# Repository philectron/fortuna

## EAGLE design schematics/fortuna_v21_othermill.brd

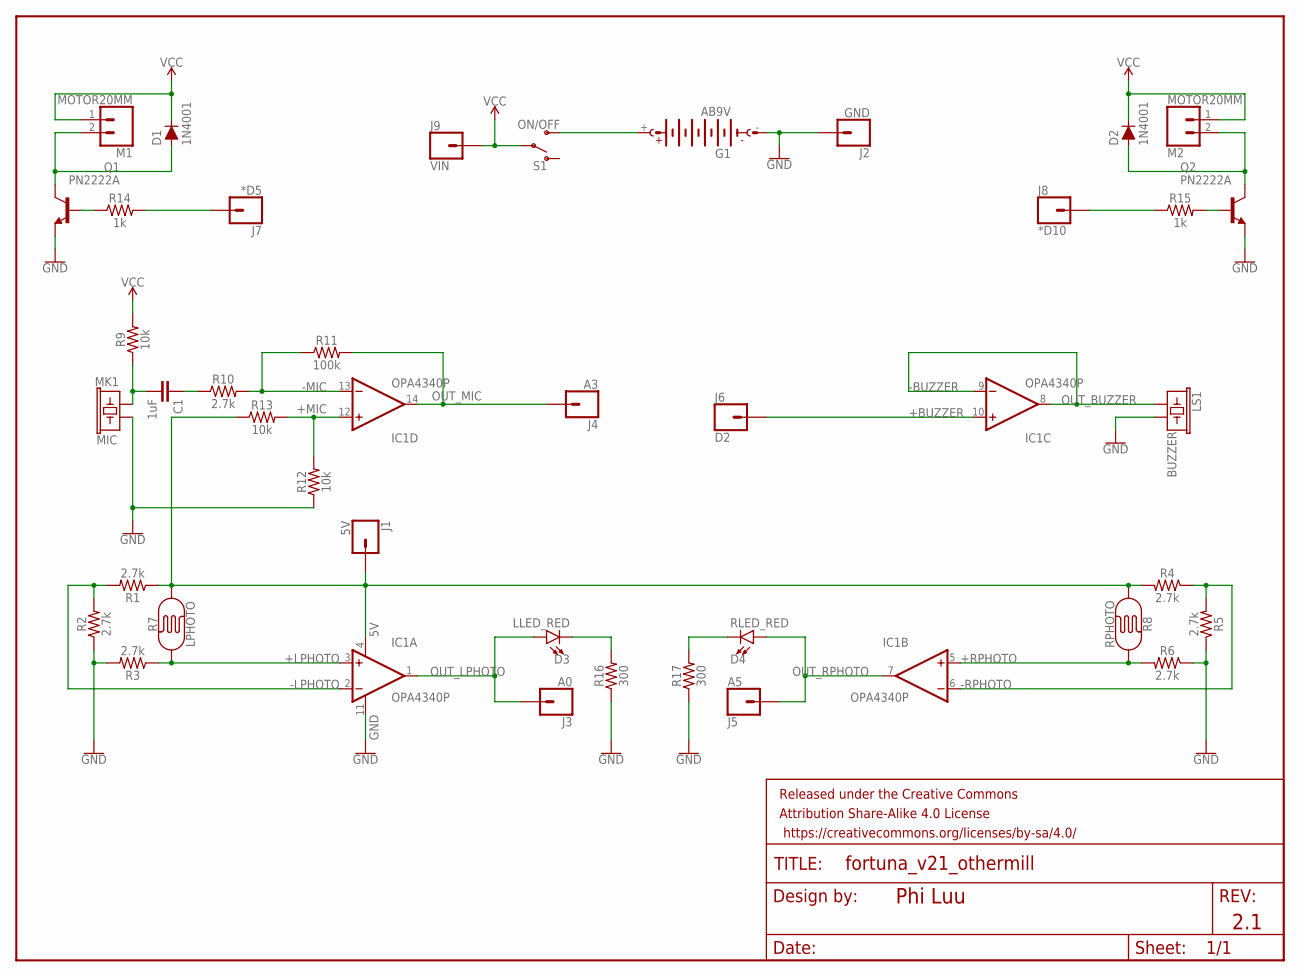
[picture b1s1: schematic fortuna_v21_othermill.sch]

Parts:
C1: 1uF; CAP-PTH-SMALL-KIT
D1, D2: 1N4001; DIODE-1N4001
D3: LLED_RED; LED_5MM
D4: RLED_RED; LED_5MM
FRAME1: FRAME-LETTER; CREATIVE_COMMONS
G1: AB9V
IC1: OPA4340P; DIL14
J1: 5V; 1X01
J2: GND; 1X01
J3: A0; 1X01
J4: A3; 1X01
J5: A5; 1X01
J6: D2; 1X01
J7: *D5; 1X01
J8: *D10; 1X01
J9: VIN; 1X01
LS1: BUZZER; BUZZER-12MM
M1, M2: MOTOR20MM; 1X02
MK1: MIC; MICROPHONE-PTH-9.7MM
Q1, Q2: PN2222A; TO92-EBC-OVAL
R1, R2, R3, R4, R5, R6, R10: 2.7k; AXIAL-0.3
R7: LPHOTO; PHOTOCELL
R8: RPHOTO; PHOTOCELL
R9, R12, R13: 10k; AXIAL-0.3
R11: 100k; AXIAL-0.3
R14, R15: 1k; AXIAL-0.3
R16, R17: 300; AXIAL-0.3
S1: ON/OFF; SWITCH_SPDT_PTH_11.6X4.0MM

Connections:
5V: IC1.4 (V+), J1.1, R1.P$1 (1), R4.P$2 (2), R7.2, R8.2, R13.P$1 (1)
9V: G1.+, S1.3 (S)
+BUZZER: IC1.10 (+IN), J6.1
+LPHOTO: IC1.3 (+IN), R3.P$1 (1), R7.1
+MIC: IC1.12 (+IN), R12.P$2 (2), R13.P$2 (2)
+RPHOTO: IC1.5 (+IN), R6.P$2 (2), R8.1
-LPHOTO: IC1.2 (-IN), R1.P$2 (2), R2.P$2 (2)
-MIC: IC1.13 (-IN), R10.P$2 (2), R11.P$1 (1)
-RPHOTO: IC1.6 (-IN), R4.P$1 (1), R5.P$2 (2)
GND: G1.-, IC1.11 (V-), J2.1, LS1.- (2), MK1.GND (2), Q1.E, Q2.E, R2.P$1 (1), R3.P$2 (2), R5.P$1 (1), R6.P$1 (1), R12.P$1 (1), R16.P$1 (1), R17.P$1 (1)
unnamed: C1.2, MK1.OUT (1), R9.P$1 (1)
unnamed: C1.1, R10.P$1 (1)
unnamed: D3.K (C), R16.P$2 (2)
unnamed: D4.K (C), R17.P$2 (2)
unnamed: Q1.B, R14.P$1 (1)
unnamed: D1.A, M1.2, Q1.C
unnamed: D2.A, M2.2, Q2.C
unnamed: Q2.B, R15.P$2 (2)
OUT_BUZZER: IC1.8 (OUT), IC1.9 (-IN), LS1.+ (1)
OUT_LMOTOR: J7.1, R14.P$2 (2)
OUT_LPHOTO: D3.A, IC1.1 (OUT), J3.1
OUT_MIC: IC1.14 (OUT), J4.1, R11.P$2 (2)
OUT_RMOTOR: J8.1, R15.P$1 (1)
OUT_RPHOTO: D4.A, IC1.7 (OUT), J5.1
VCC: D1.C, D2.C, J9.1, M1.1, M2.1, R9.P$2 (2), S1.2

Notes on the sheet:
Phi Luu
2.1
+BUZZER
-BUZZER

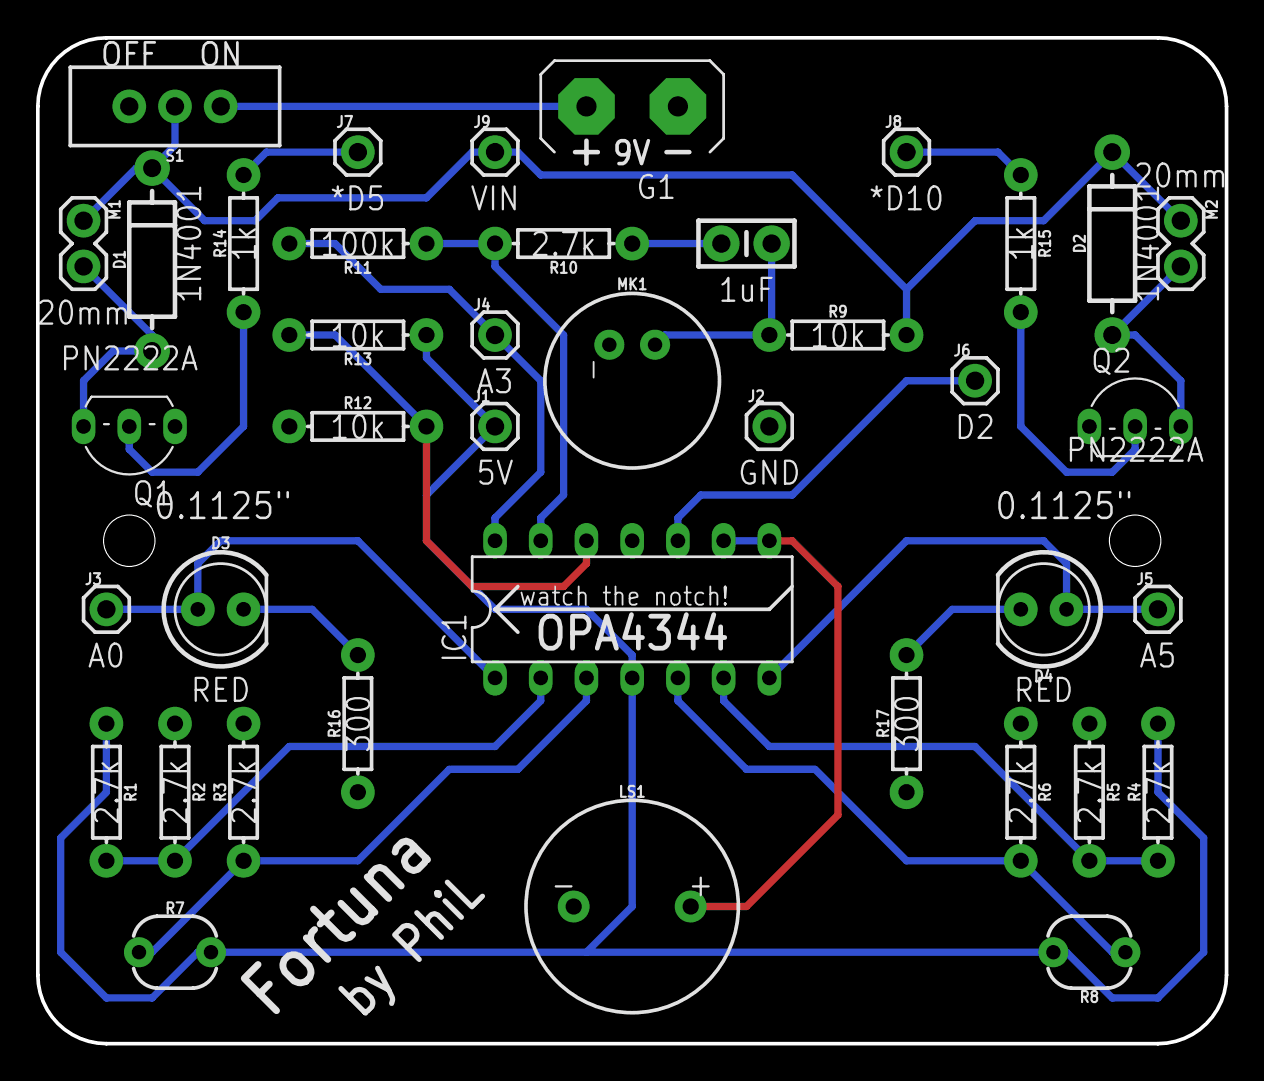
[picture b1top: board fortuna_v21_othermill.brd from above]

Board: 2 copper layers, 66.0 x 55.9 mm, 41 parts (0 on the bottom side), 25 nets.

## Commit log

2017-10-09 Create a separate repo for Fortuna
2017-10-16 Use images for documentation rather than EAGLE files
    Using EAGLE files doesn't help since GitHub only displays raw code of the files, which is in EALGE language. It also makes the language ratio hugely inclined towards EAGLE.
2017-10-17 Replace with smaller-size image
2017-11-02 Improve file comments
2017-11-13 Beautify code. Disable alignments.
2017-11-15 Remove MIT License
2017-11-15 Create MIT License
2018-01-14 Add Linux & macOS
2018-02-07 Ignore the .vscode folder generated by VS Code

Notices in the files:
parts and their libraries:
SparkFun-Capacitors: Licensing: Creative Commons ShareAlike 4.0 International - https://creativecommons.org/licenses/by-sa/4.0
SparkFun-Aesthetics: Released under the Creative Commons Attribution Share-Alike 4.0 License
SparkFun-Aesthetics: https://creativecommons.org/licenses/by-sa/4.0
